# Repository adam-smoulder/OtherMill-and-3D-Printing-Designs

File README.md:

# OtherMill-and-3D-Printing-Designs
A place to keep all my project designs for the OtherMill and 3D printers in B09 Benedum Hall.

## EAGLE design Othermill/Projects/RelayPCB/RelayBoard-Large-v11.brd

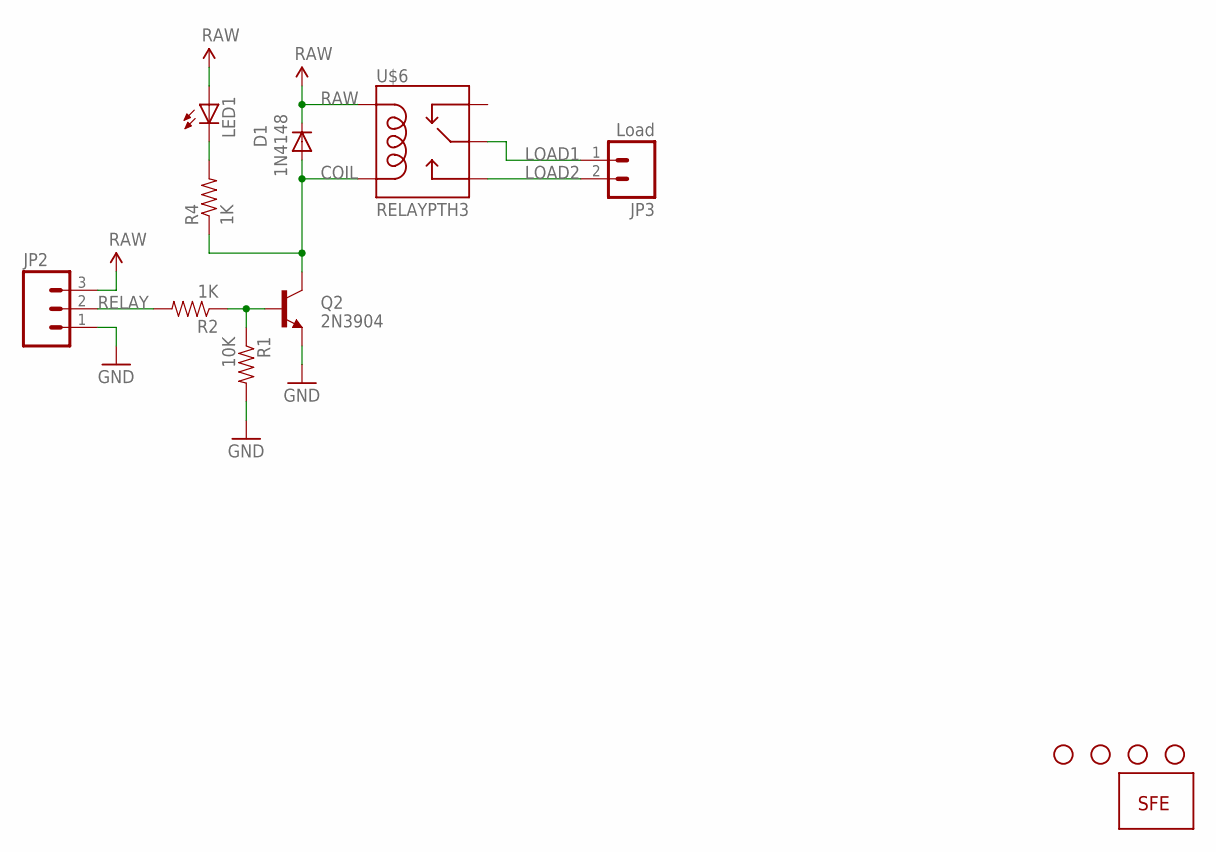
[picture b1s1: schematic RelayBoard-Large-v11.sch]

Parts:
D1: 1N4148; DIODE-1N4148
JP2: M03SCREW; SCREWTERMINAL-3.5MM-3
JP3: Load; SCREWTERMINAL-5MM-2
LED1: LED5MM
Q2: 2N3904; TO-92
R1: 10K; AXIAL-0.3
R2, R4: 1K; AXIAL-0.3
U$1: LOGO-SFENEW; SFE-NEW-WEBLOGO
U$3, U$4, U$5, U$7: STAND-OFF
U$6: RELAYPTH3; RELAY-T9A-2

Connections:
COIL: D1.A, Q2.3 (C), R4.P$1 (1), U$6.COIL2
GND: JP2.1, Q2.1 (E), R1.P$2 (2)
LOAD1: JP3.1, U$6.MAIN
LOAD2: JP3.2, U$6.NO
unnamed: Q2.2 (B), R1.P$1 (1), R2.P$1 (1)
unnamed: LED1.K (C), R4.P$2 (2)
RAW: D1.C, JP2.3, LED1.A, U$6.COIL1
RELAY: JP2.2, R2.P$2 (2)

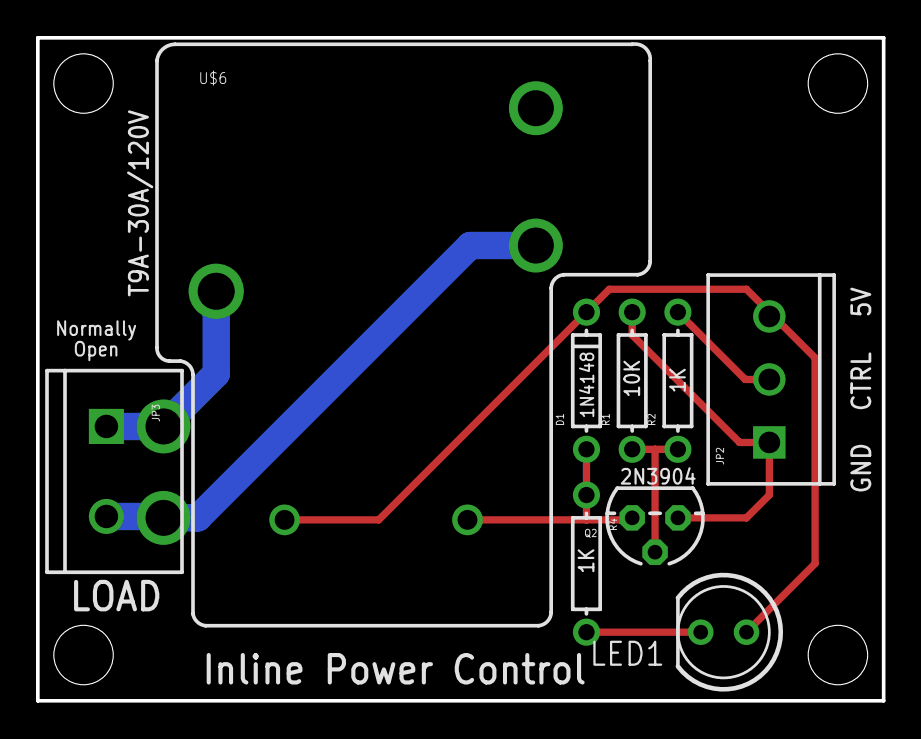
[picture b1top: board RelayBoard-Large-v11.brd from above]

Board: 2 copper layers, 47.0 x 36.8 mm, 14 parts (1 on the bottom side), 8 nets.

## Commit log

2017-08-11 added files circa 8/11/17
